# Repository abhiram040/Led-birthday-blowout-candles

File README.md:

# Led-birthday-candles
Light up led birthday candles arranged in rows with batttery power supply and blow them.... The number of leds are controlled using bluetooth from mobile phone depending upon age.  This project uses msp430g2553 micocontroller to control leds arranged in matrix form.  Once power leds's flicker as candles.  led's can be blown off as a real candles by sensing the temperature change using thermister.

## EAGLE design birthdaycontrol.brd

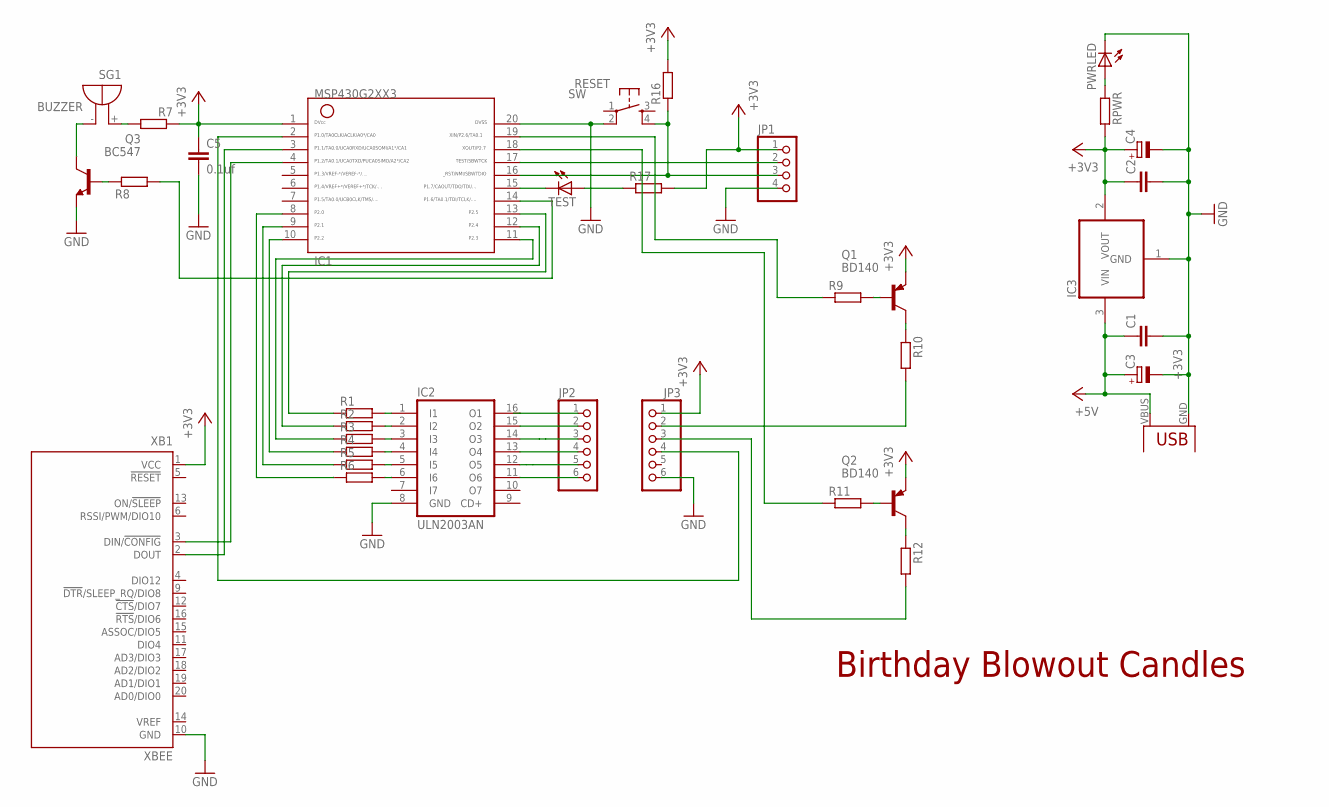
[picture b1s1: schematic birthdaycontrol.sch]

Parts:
C1, C2: C-EU025-025X050; C025-025X050
C3, C4: CPOL-EUE2.5-5; E2,5-5
C5: 0.1uf; C025-025X050
IC1: MSP430; G2553-DIP20
IC2: ULN2003AN; DIL16
IC3: REG1117; SOT223
JP1: PINHD-1X4; 1X04
JP2, JP3: PINHD-1X6; 1X06
PWRLED: LED3MM
Q1, Q2: BD140; TO126
Q3: BC547; TO92
R1, R2, R3, R4, R5, R6, R7, R8, R9, R10, R11, R12, R16, R17: R-EU_0207/7; 0207/7
RESET: SW; B3F-10XX
RPWR: R-EU_0207/7; 0207/7
SG1: BUZZER; F/TMB
TEST: LED3MM
U$6: USB(POWER)
XB1: XBEE

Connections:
+3V3: C2.1, C4.+, C5.1, IC1.1, IC3.2 (VOUT), JP1.1, JP3.1, Q1.1 (E), Q2.1 (E), R7.1, R16.2, R17.2, RPWR.2, XB1.1 (VCC)
+5V: C1.1, C3.+, IC3.3 (VIN), U$6.VBUS (VCC)
GND: C1.2, C2.2, C3.-, C4.-, C5.2, IC1.20, IC2.8 (GND), IC3.1 (GND), JP1.4, JP3.6, PWRLED.K (C), Q3.1 (E), RESET.2 (P1), U$6.GND, XB1.10 (GND)
unnamed: IC1.18, R11.1
unnamed: IC1.3, XB1.2 (DOUT)
unnamed: IC2.1 (I1), R1.2
unnamed: IC2.2 (I2), R2.2
unnamed: Q1.3 (B), R9.2
unnamed: Q1.2 (C), R10.1
unnamed: IC1.15, TEST.K (C)
unnamed: R17.1, TEST.A
unnamed: IC2.3 (I3), R3.2
unnamed: Q3.3 (C), SG1.-
unnamed: IC2.4 (I4), R4.2
unnamed: R7.2, SG1.+
unnamed: IC2.5 (I5), R5.2
unnamed: IC2.6 (I6), R6.2
unnamed: IC1.8, R6.1
unnamed: IC1.9, R5.1
unnamed: IC1.10, R4.1
unnamed: IC1.11, R3.1
unnamed: Q3.2 (B), R8.1
unnamed: IC1.12, R2.1
unnamed: IC1.13, R1.1
unnamed: Q2.3 (B), R11.2
unnamed: Q2.2 (C), R12.1
unnamed: IC2.13 (O4), JP2.4
unnamed: IC1.4, XB1.3 (DIN/!CONFIG)
unnamed: IC2.16 (O1), JP2.1
unnamed: IC2.12 (O5), JP2.5
unnamed: IC1.2, JP3.4
unnamed: PWRLED.A, RPWR.1
unnamed: IC2.15 (O2), JP2.2
unnamed: IC2.14 (O3), JP2.3
unnamed: JP3.3, R12.2
unnamed: IC2.11 (O6), JP2.6
unnamed: JP3.2, R10.2
unnamed: IC1.19, R9.1
P1.2: IC1.14, R8.2
RST: IC1.16, JP1.3, R16.1, RESET.4 (S1)
TEST: IC1.17, JP1.2

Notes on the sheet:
Birthday Blowout Candles

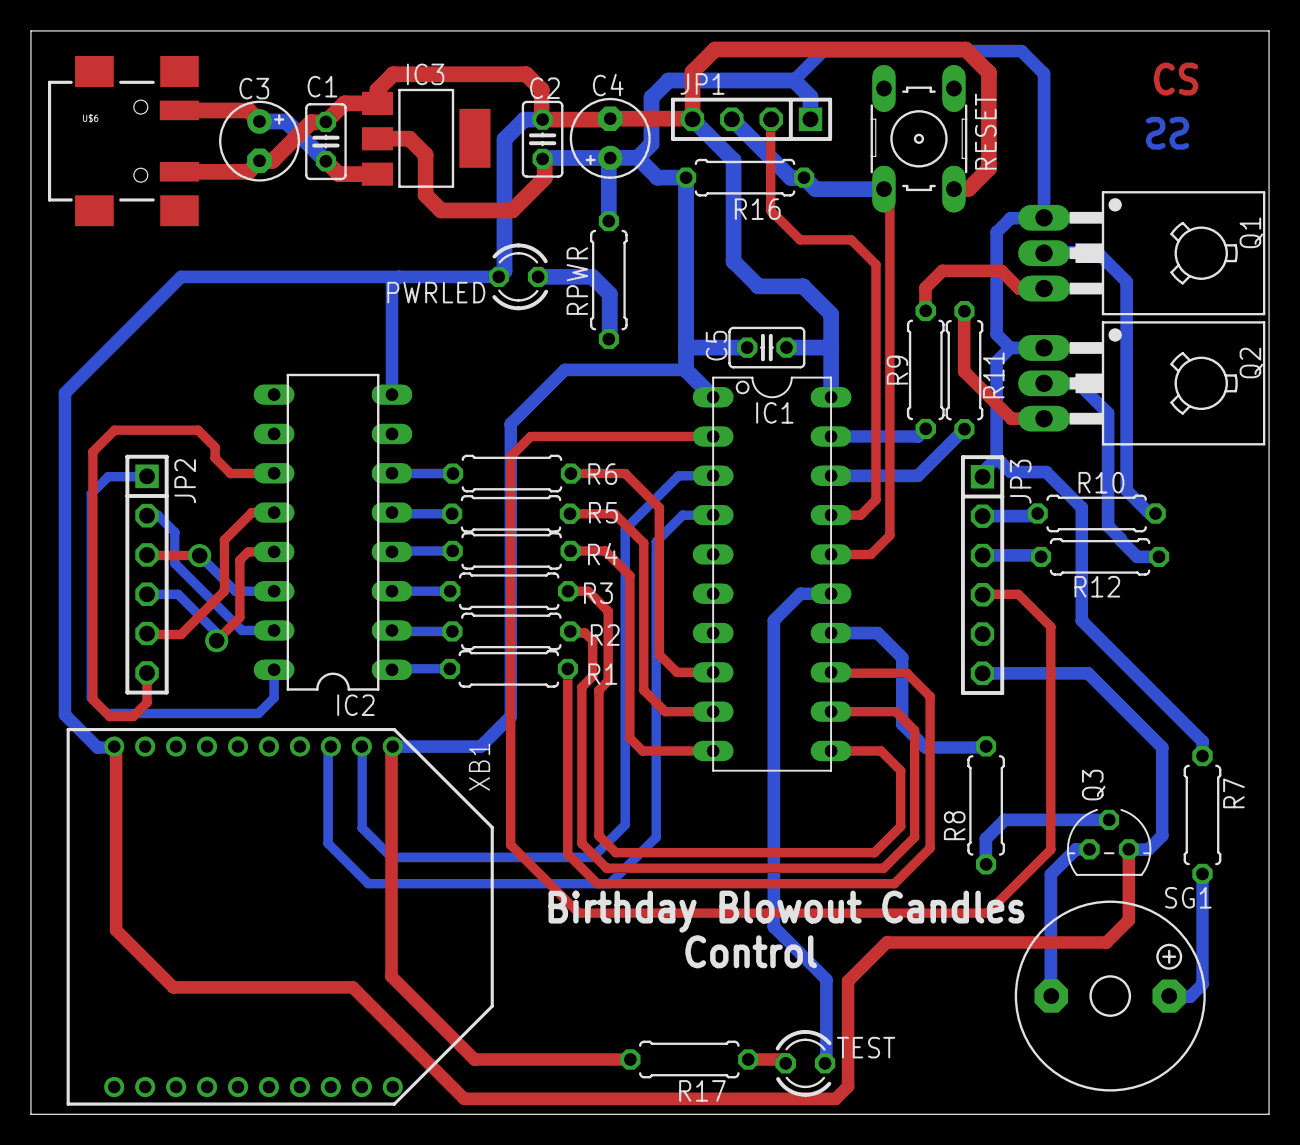
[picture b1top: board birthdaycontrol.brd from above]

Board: 2 copper layers, 80.0 x 70.0 mm, 35 parts (0 on the bottom side), 41 nets.

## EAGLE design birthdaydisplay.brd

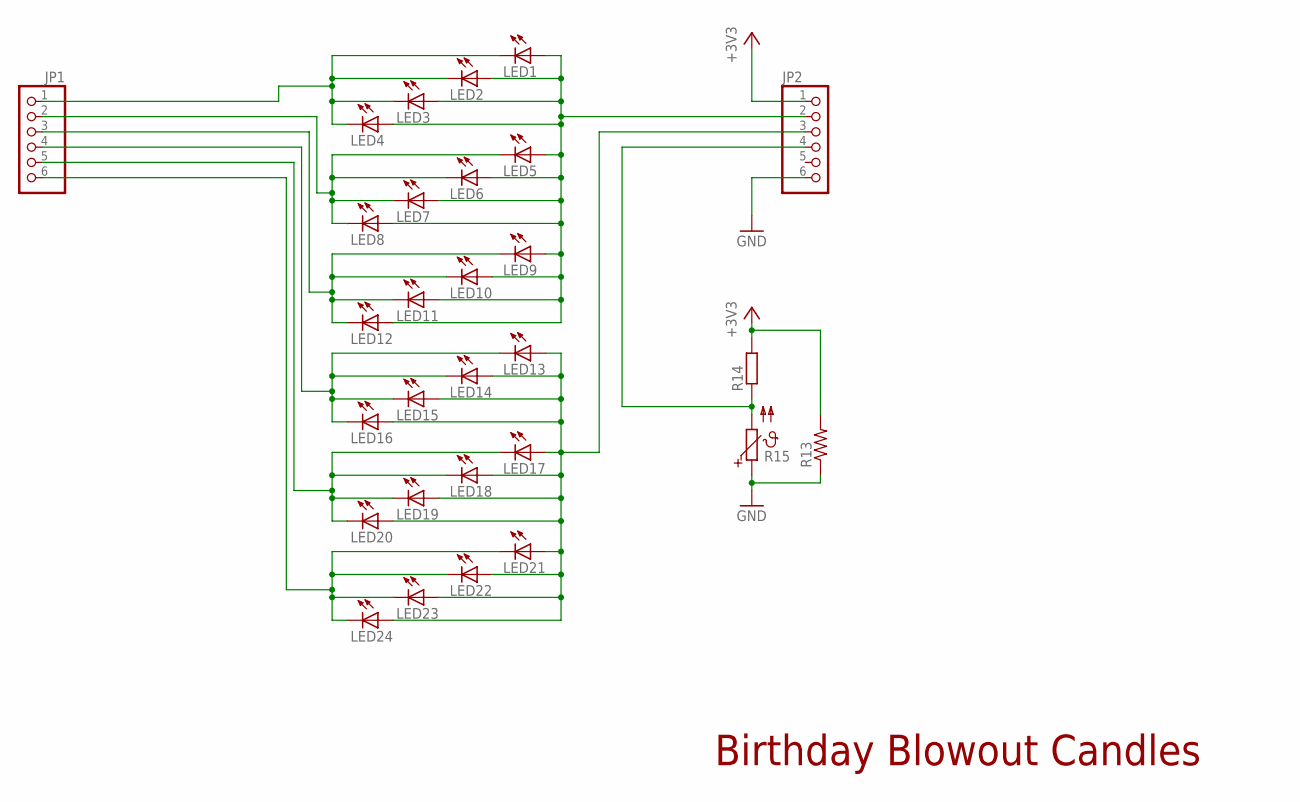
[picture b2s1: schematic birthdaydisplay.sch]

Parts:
JP1, JP2: PINHD-1X6; 1X06
LED1, LED2, LED3, LED4, LED5, LED6, LED7, LED8, LED9, LED10, LED11, LED12, LED13, LED14, LED15, LED16, LED17, LED18, LED19, LED20, LED21, LED22, LED23, LED24: LED3MM
R13: R-US_0207/10; 0207/10
R14: R-EU_0207/7; 0207/7
R15: PTC679; P679

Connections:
+3V3: JP2.1, R13.2, R14.2
GND: JP2.6, R13.1, R15.1
unnamed: JP1.4, LED13.K (C), LED14.K (C), LED15.K (C), LED16.K (C)
unnamed: JP2.4, R14.1, R15.2
unnamed: JP1.1, LED1.K (C), LED2.K (C), LED3.K (C), LED4.K (C)
unnamed: JP1.2, LED5.K (C), LED6.K (C), LED7.K (C), LED8.K (C)
unnamed: JP2.2, LED1.A, LED2.A, LED3.A, LED4.A, LED5.A, LED6.A, LED7.A, LED8.A, LED9.A, LED10.A, LED11.A, LED12.A
unnamed: JP1.3, LED9.K (C), LED10.K (C), LED11.K (C), LED12.K (C)
unnamed: JP1.5, LED17.K (C), LED18.K (C), LED19.K (C), LED20.K (C)
unnamed: JP2.3, LED13.A, LED14.A, LED15.A, LED16.A, LED17.A, LED18.A, LED19.A, LED20.A, LED21.A, LED22.A, LED23.A, LED24.A
unnamed: JP1.6, LED21.K (C), LED22.K (C), LED23.K (C), LED24.K (C)

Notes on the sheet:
Birthday Blowout Candles

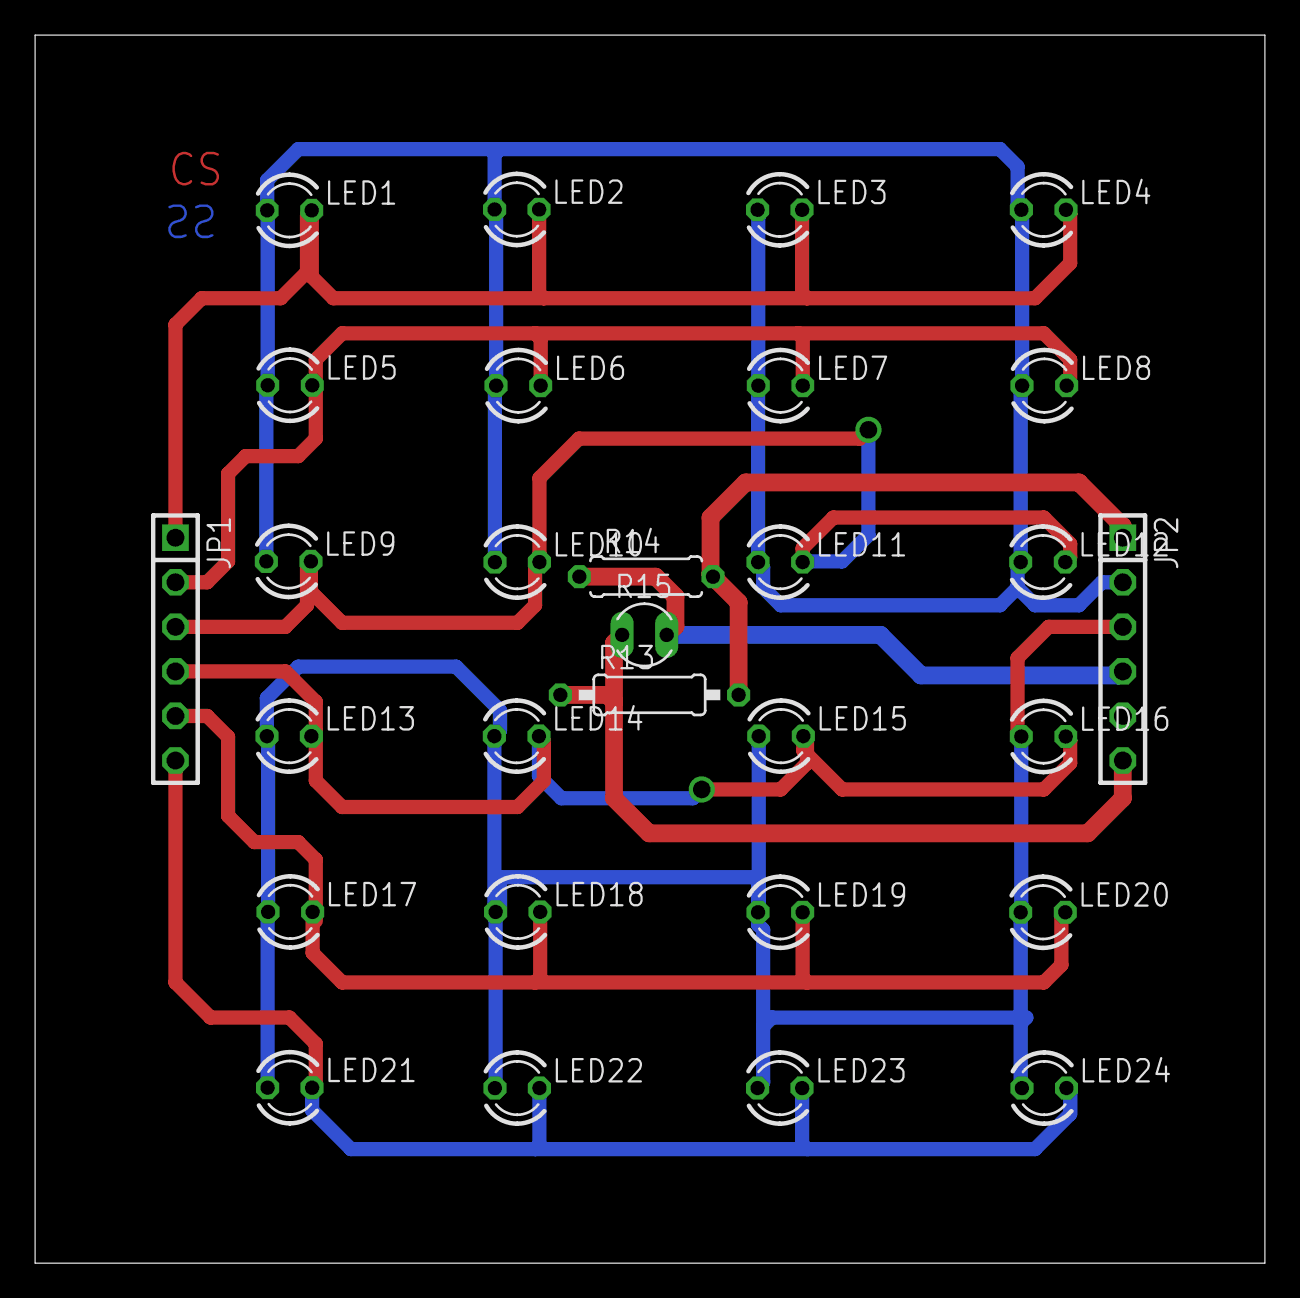
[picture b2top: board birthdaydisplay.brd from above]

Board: 2 copper layers, 70.1 x 70.0 mm, 29 parts (0 on the bottom side), 11 nets.

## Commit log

2018-06-18 Create PCB schematic and layout

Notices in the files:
parts and their libraries:
SparkFun-Aesthetics: Licensing: Creative Commons ShareAlike 4.0 International - https://creativecommons.org/licenses/by-sa/4.0
